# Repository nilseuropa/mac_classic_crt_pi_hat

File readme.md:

## Classic Mac CRT driver HAT for Raspberry Pi4

:warning: **Proof of concept running PoP on minivmac:**

This method is utilizing the Display Parallel Interface of the RPi. The DPI device tree overlay has to be configured correctly to make this work. *(For fine tuning, troubleshooting or more detailed explanation please follow the link in the credits section to **nerdhut**'s original article.)* :arrow_left: KUDOS

### Configuration
```
dtoverlay=dpi24
overscan_left=0
overscan_right=0
overscan_top=0
overscan_bottom=0
framebuffer_width=512
framebuffer_height=342
enable_dpi_lcd=1
display_default_lcd=1
dpi_group=2
dpi_mode=87
dpi_output_format=0x76017
dpi_timings=512 0 14 178 0 342 0 0 4 24 0 0 0 60 0 15667200 1
```

### Schematics
Theoretically you can invert the data signal by just configuring the video hardware, but instead of that I have decided to sum the highest bits of the green, blue and red channels through an inverter IC. *( It could have been just 3 transistors. )*

### Board layout
The board has been quickly put together as an afternoon project. The goal was to quickly make a single sided prototype version based on DIP components. Feel free to edit the eagle source files included in this repository to your needs.

#### Top side

#### Bottom side

### Build
As this was a quick and dirty build, I have just mounted the RPi with it's connectors facing outwards to a depron plate, held by a piece of aluminium angle that was lying around. This way I have access to the ethernet and USB ports.

 I used a cheap SD Card extension cable, so that I can fiddle with the card without disassembling the whole contraption. *( I have reused the DSUB connector in my Apple // --- nothing goes to waste here ... :smile: )*

### Final result

### Further plans *( big ideas, don't get any )*
* Currently the ADB connectors are hooked up through a microcontroller, that is totally unnecessary, the interface could go straight to the HAT instead.
* An additional SPI USB controller chip could be added to the HAT, supporting USB-SCSI.
* It would be nice to interface the floppy drive *( maybe through an integrated greaseweazle )*
* Another idea is to add an analog amplifier as well, so that the internal speaker is driven directly by the SBC. ( ... and the audio jacks )
* The whole thing could go in place of the original motherboard, with the connector interface matching the holes on the enclosure.

### Credits
Most credits go to **nerdhut** for doing all the heavy lifting. A truly elegant solution. :clap:
https://nerdhut.de/2020/03/17/raspberry-pi-dpi-control-crt/

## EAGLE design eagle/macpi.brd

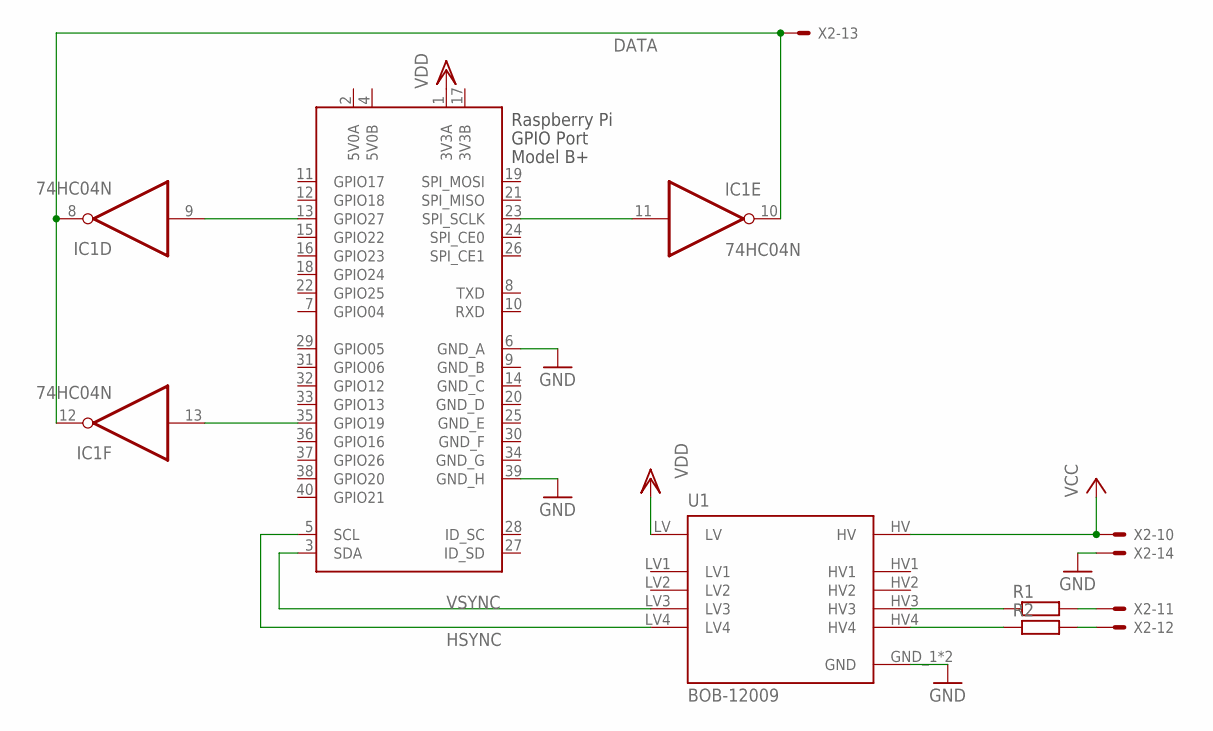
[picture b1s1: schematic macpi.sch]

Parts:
IC1: 74HC04N; DIL14
R1, R2: R-EU_VMTA55; VMTA55
U1: BOB-12009; CONV_BOB-12009
X1: RASPI_GPIO_B+#_PIN; RASPI_GPIO_B+_PIN
X2: 5566-14

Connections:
3V3B: X1.17 (3V3B)
5V0A: X1.2 (5V0A)
5V0B: X1.4 (5V0B)
DATA: IC1.8 (O), IC1.10 (O), IC1.12 (O), X2.13
GND: IC1.7 (GND), U1.GND_1 (GND), U1.GND_2 (GND), X1.6 (GND_A), X1.39 (GND_H), X2.14
GND_B: X1.9 (GND_B)
GND_C: X1.14 (GND_C)
GND_D: X1.20 (GND_D)
GND_E: X1.25 (GND_E)
GND_F: X1.30 (GND_F)
GND_G: X1.34 (GND_G)
HSYNC: U1.LV4, X1.5 (SCL)
unnamed: IC1.11 (I), X1.23 (SPI_SCLK)
unnamed: IC1.9 (I), X1.13 (GPIO27)
unnamed: IC1.13 (I), X1.35 (GPIO19)
unnamed: R2.1, U1.HV4
unnamed: R1.2, X2.11
unnamed: R1.1, U1.HV3
unnamed: R2.2, X2.12
VCC: IC1.14 (VCC), U1.HV, X2.10
VDD: U1.LV, X1.1 (3V3A)
VSYNC: U1.LV3, X1.3 (SDA)

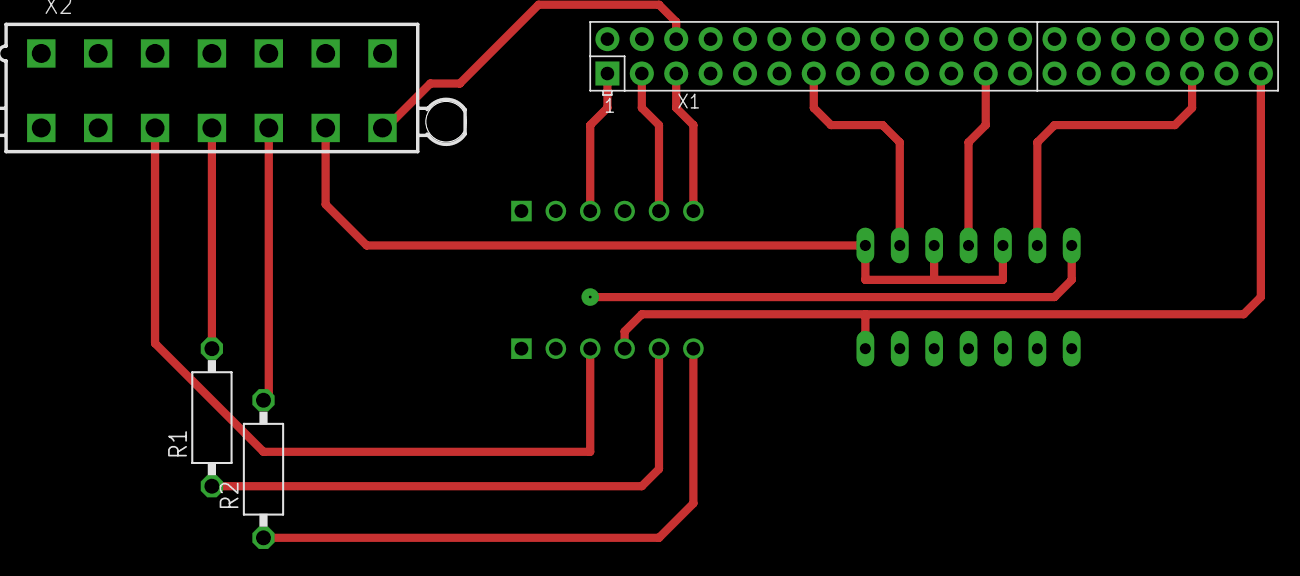
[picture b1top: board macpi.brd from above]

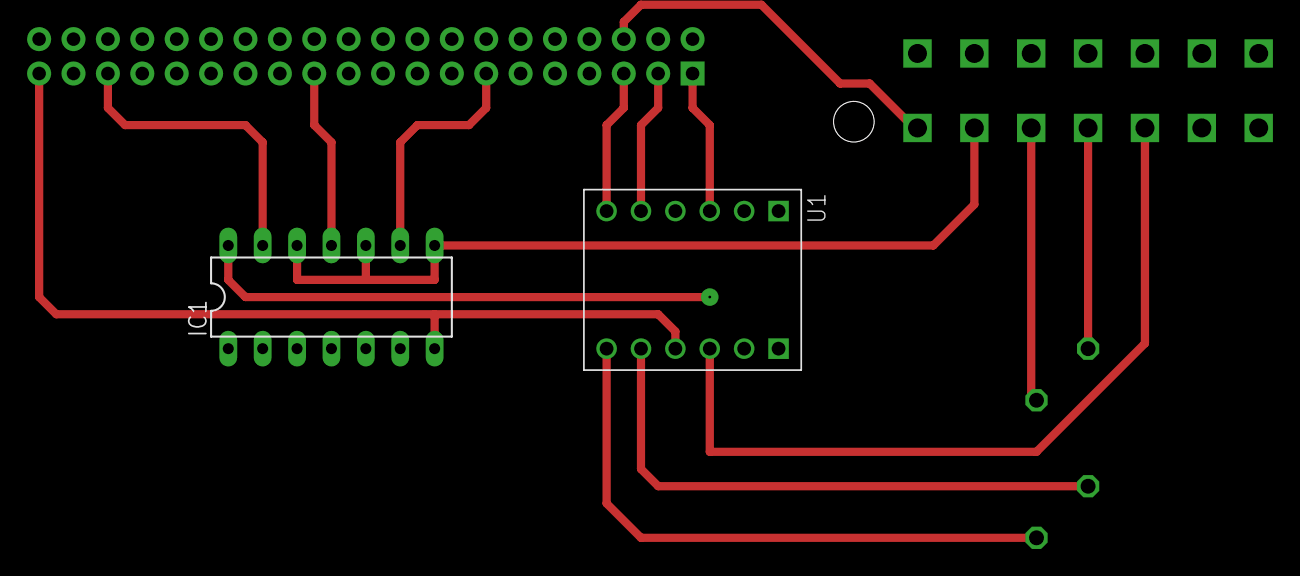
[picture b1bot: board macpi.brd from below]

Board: 2 copper layers, 6 parts (2 on the bottom side), 13 nets.

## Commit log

2024-02-04 that's that
